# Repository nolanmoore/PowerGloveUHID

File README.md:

## Intro

In a world... where wires are a thing of the past, pound signs are now hashtags and there is always a “new black,” one man will revive a gaming icon in order to preserve the past… and control the future.

The ultimate goal of the Power Glove UHID (Universal Human Interface Device) project is to revamp the 1989 Nintendo Power Glove with modern sensors, giving you the ability to use gesture controls with almost anything you can think of, in style.

Check out the [Hackaday.io project page](https://hackaday.io/project/8455-power-glove-uhid) for more info!

## Revisions

### Main Board
* Rev 0.1 (current): Complete! Features custom keypad, Teensy 3/LC header, ESP-12E/01 headers and Pololu 3.3V step up/down regulator.<br />
Top side:<br />
<br />
Bottom side:<br />

### Sensor Board
* Rev 0.1 (current): Unfinished WIP. Along with the existing flex sensors, the current prototype sensor board will feature a Pololu AltIMU-10 as the main sensor.

## License

This is an open hardware design licensed under the terms of the CERN Open Hardware Licence (OHL) v1.2.

You may redistribute and modify this documentation under the terms of the CERN OHL v.1.2 (http://ohwr.org/cernohl). This documentation is distributed WITHOUT ANY EXPRESS OR IMPLIED WARRANTY, INCLUDING OF MERCHANTABILITY, SATISFACTORY QUALITY AND FITNESS FOR A PARTICULAR PURPOSE. Please see the CERN OHL v.1.2 for applicable conditions.

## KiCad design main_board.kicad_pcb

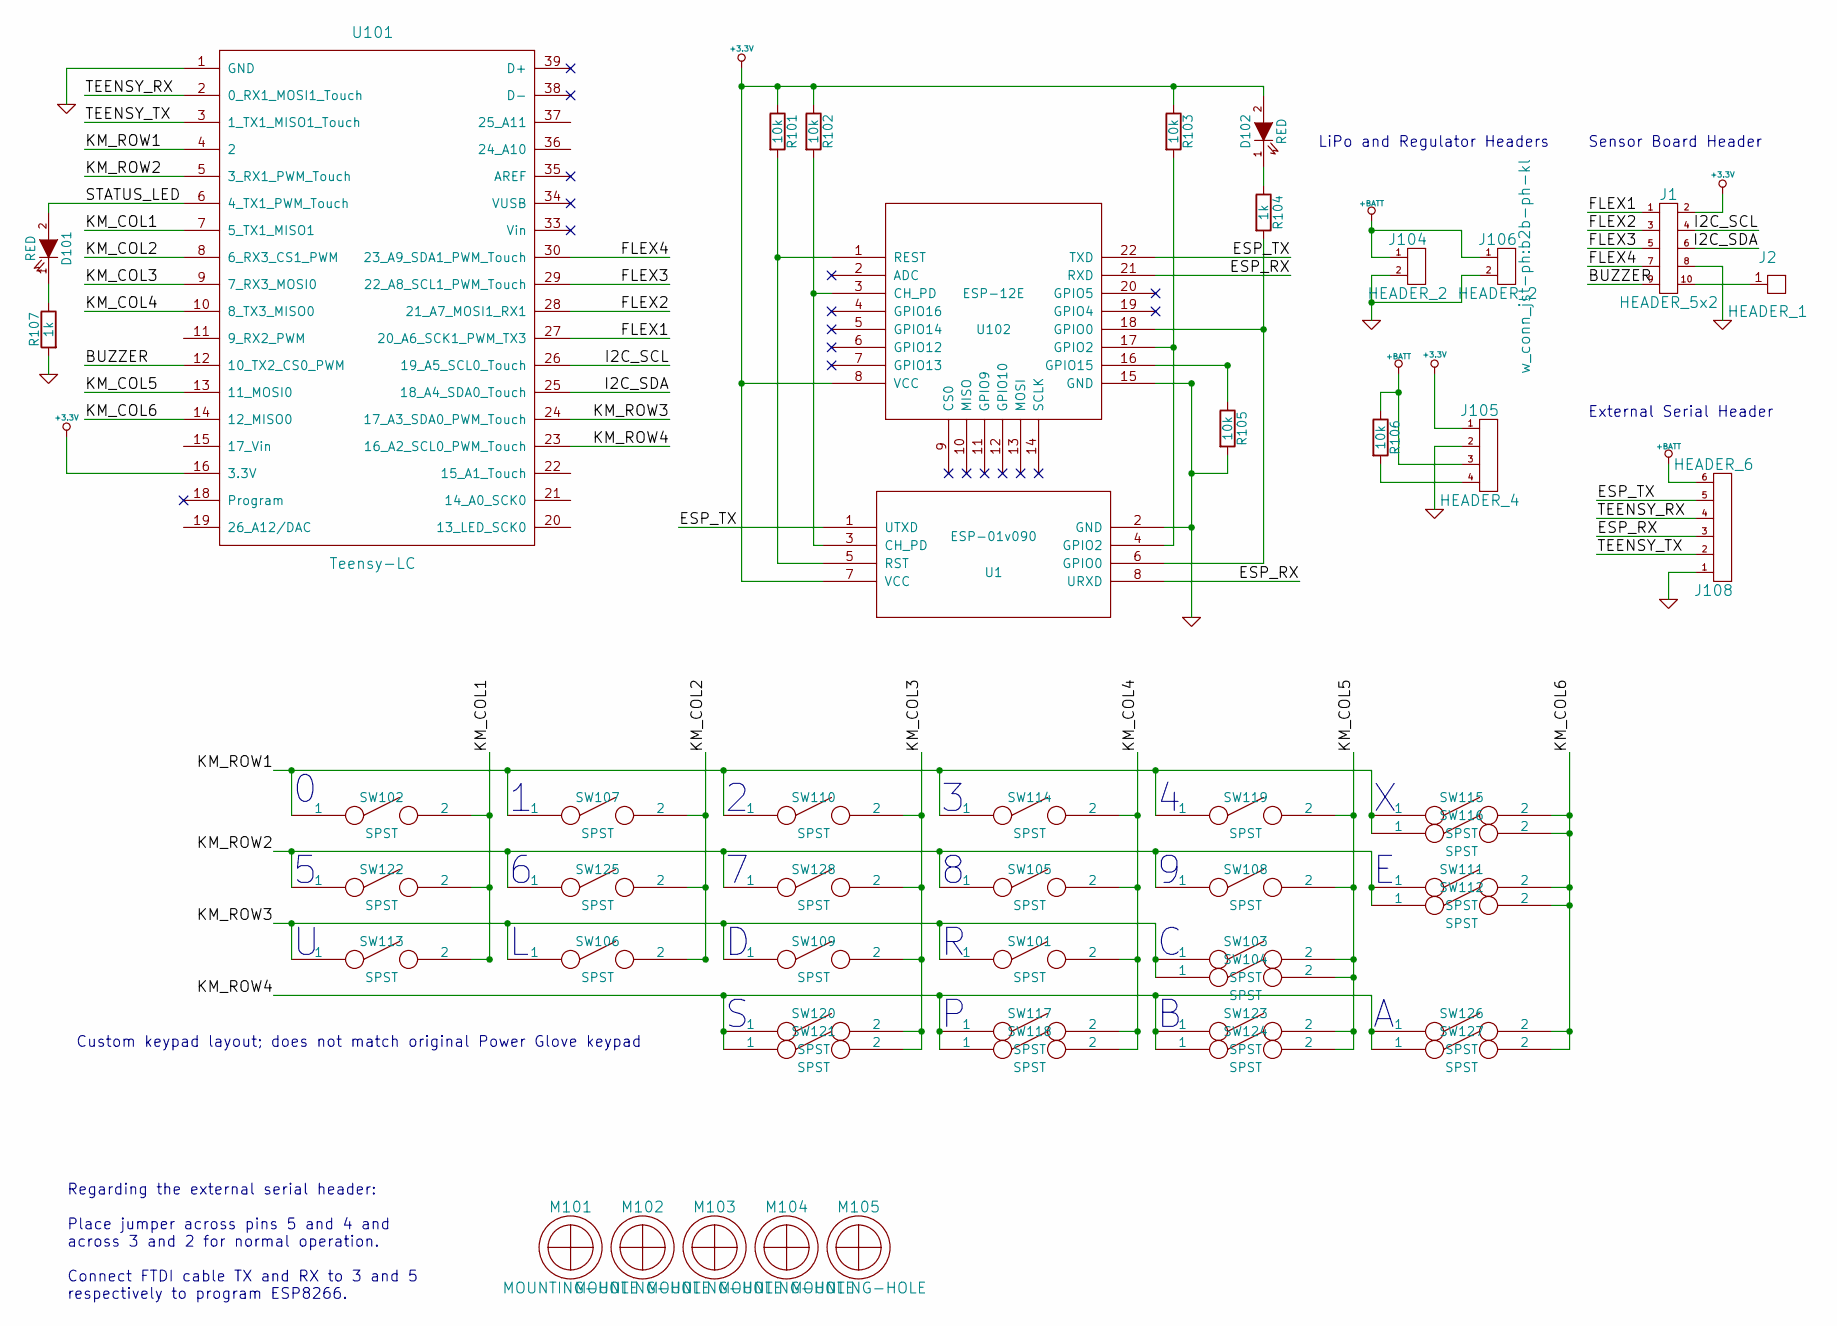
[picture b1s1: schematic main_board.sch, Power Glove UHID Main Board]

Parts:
D101: RED; LED-3MM
D102: RED; LED_0805
J1: HEADER_5x2; Socket_Strip_Straight_2x05
J2: HEADER_1; Socket_Strip_Straight_1x01
J104: HEADER_2; Socket_Strip_Straight_1x02
J105: HEADER_4; Socket_Strip_Straight_1x04
J106: HEADER_2; b2b-ph-kl
J108: HEADER_6; Pin_Header_Angled_1x06
M101, M102, M103, M104, M105: MOUNTING-HOLE; MountingHole_2-2mm
R101, R102, R103, R105, R106: 10k; R_0805
R104, R107: 1k; R_0805
SW101, SW106, SW109, SW113: SPST; CONDUCTIVE-PAD-HALFSHELL-150MIL
SW102, SW103, SW104, SW105, SW107, SW108, SW110, SW111, SW112, SW114, SW115, SW116, SW117, SW118, SW119, SW120, SW121, SW122, SW123, SW124, SW125, SW126, SW127, SW128: SPST; CONDUCTIVE-PAD-STANDARD-150MIL
U1: ESP-01v090; ESP-01
U101: Teensy-LC; Teensy3.x_LC
U102: ESP-12E

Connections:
+3.3V: D102.2 (A), J1.2, J105.1, R101.1, R102.1, R103.1, U1.7 (VCC), U101.16 (3.3V), U101.31 (3.3V), U102.8 (VCC)
+BATT: J104.1, J105.3, J106.1, J108.6, R106.1
/BUZZER: J1.9, U101.12 (10_TX2_CS0_PWM)
/ESP_RX: J108.3, U1.8 (URXD), U102.21 (RXD)
/ESP_TX: J108.5, U1.1 (UTXD), U102.22 (TXD)
/FLEX1: J1.1, U101.27 (20_A6_SCK1_PWM_TX3)
/FLEX2: J1.3, U101.28 (21_A7_MOSI1_RX1)
/FLEX3: J1.5, U101.29 (22_A8_SCL1_PWM_Touch)
/FLEX4: J1.7, U101.30 (23_A9_SDA1_PWM_Touch)
/I2C_SCL: J1.4, U101.26 (19_A5_SCL0_Touch)
/I2C_SDA: J1.6, U101.25 (18_A4_SDA0_Touch)
/KM_COL1: SW102.2, SW113.2, SW122.2, U101.7 (5_TX1_MISO1)
/KM_COL2: SW106.2, SW107.2, SW125.2, U101.8 (6_RX3_CS1_PWM)
/KM_COL3: SW109.2, SW110.2, SW120.2, SW121.2, SW128.2, U101.9 (7_RX3_MOSI0)
/KM_COL4: SW101.2, SW105.2, SW114.2, SW117.2, SW118.2, U101.10 (8_TX3_MISO0)
/KM_COL5: SW103.2, SW104.2, SW108.2, SW119.2, SW123.2, SW124.2, U101.13 (11_MOSI0)
/KM_COL6: SW111.2, SW112.2, SW115.2, SW116.2, SW126.2, SW127.2, U101.14 (12_MISO0)
/KM_ROW1: SW102.1, SW107.1, SW110.1, SW114.1, SW115.1, SW116.1, SW119.1, U101.4 (2)
/KM_ROW2: SW105.1, SW108.1, SW111.1, SW112.1, SW122.1, SW125.1, SW128.1, U101.5 (3_RX1_PWM_Touch)
/KM_ROW3: SW101.1, SW103.1, SW104.1, SW106.1, SW109.1, SW113.1, U101.24 (17_A3_SDA0_PWM_Touch)
/KM_ROW4: SW117.1, SW118.1, SW120.1, SW121.1, SW123.1, SW124.1, SW126.1, SW127.1, U101.23 (16_A2_SCL0_PWM_Touch)
/STATUS_LED: D101.2 (A), U101.6 (4_TX1_PWM_Touch)
/TEENSY_RX: J108.4, U101.2 (0_RX1_MOSI1_Touch)
/TEENSY_TX: J108.2, U101.3 (1_TX1_MISO1_Touch)
GND: J1.8, J104.2, J105.2, J106.2, J108.1, R105.2, R107.2, U1.2 (GND), U101.1 (GND), U101.17 (GND), U101.32 (GND), U102.15 (GND)
unnamed: D101.1 (K), R107.1
unnamed: D102.1 (K), R104.1
unnamed: J1.10, J2.1
unnamed: J105.4, R106.2
unnamed: R101.2, U1.5 (RST), U102.1 (REST)
unnamed: R102.2, U1.3 (CH_PD), U102.3 (CH_PD)
unnamed: R103.2, U1.4 (GPIO2), U102.17 (GPIO2)
unnamed: R104.2, U1.6 (GPIO0), U102.18 (GPIO0)
unnamed: R105.1, U102.16 (GPIO15)

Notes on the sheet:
Sensor Board Header
LiPo and Regulator Headers
Custom keypad layout; does not match original Power Glove keypad
External Serial Header
Regarding the external serial header: Place jumper across pins 5 and 4 and across 3 and 2 for normal operation. Connect FTDI cable TX and RX to 3 and 5 respectively to program ESP8266.

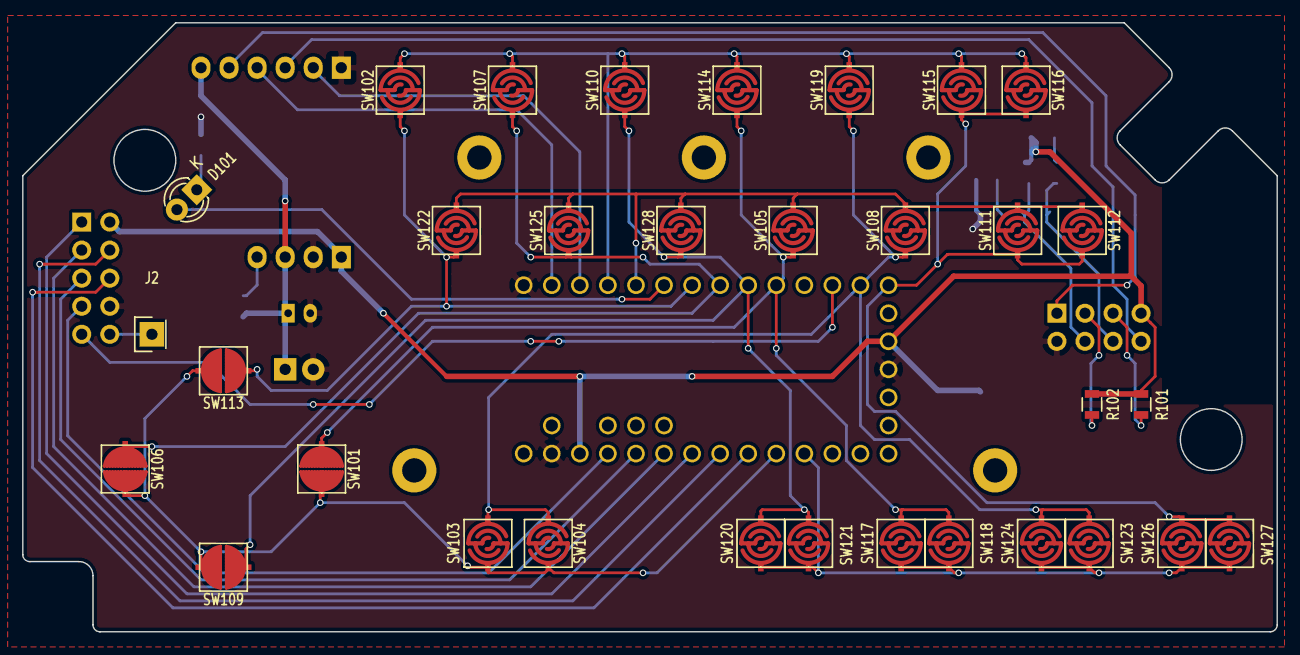
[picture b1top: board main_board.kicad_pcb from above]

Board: 2 copper layers, 113.5 x 55.1 mm, 51 parts (0 on the bottom side), 34 nets.

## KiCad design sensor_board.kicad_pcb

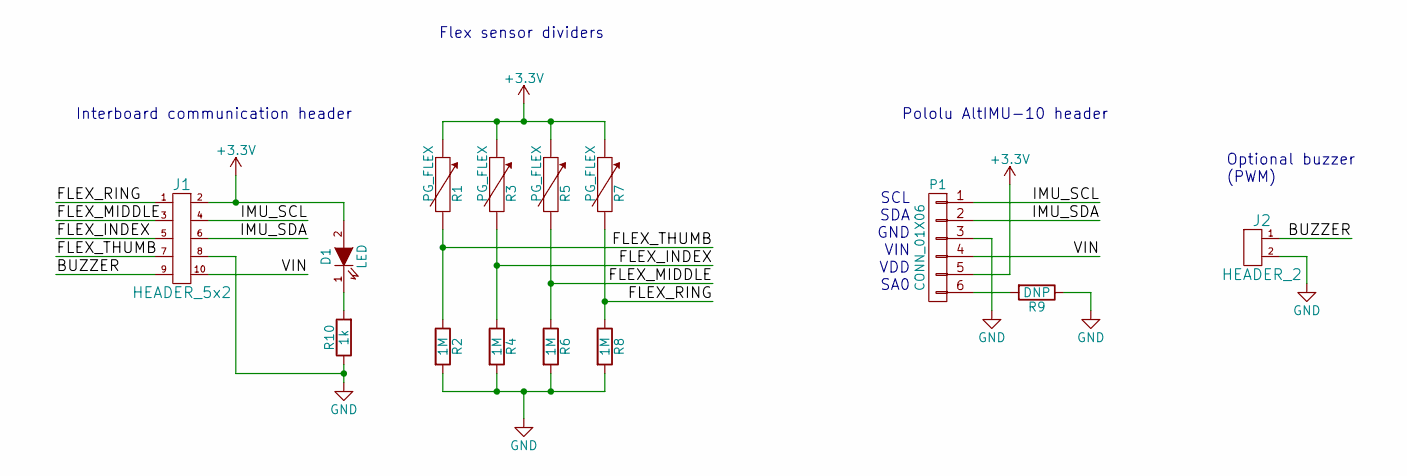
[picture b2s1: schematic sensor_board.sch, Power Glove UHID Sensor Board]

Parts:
D1: LED; Led_0805
J1: HEADER_5x2; Socket_Strip_Straight_2x05
J2: HEADER_2; Socket_Strip_Straight_1x02
P1: CONN_01X06; ALTIMU10
R1, R3, R5, R7: PG_FLEX; Socket_Strip_Straight_1x02
R2, R4, R6, R8: 1M; Resistor_Horizontal_RM10mm
R9: DNP; R_0805_HandSoldering
R10: 1k; R_0805_HandSoldering

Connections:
+3V3: D1.2 (A), J1.2, P1.5, R1.1, R3.1, R5.1, R7.1
/BUZZER: J1.9, J2.1
/FLEX_INDEX: J1.5, R3.2, R4.1
/FLEX_MIDDLE: J1.3, R5.2, R6.1
/FLEX_RING: J1.1, R7.2, R8.1
/FLEX_THUMB: J1.7, R1.2, R2.1
/IMU_SCL: J1.4, P1.1
/IMU_SDA: J1.6, P1.2
/VIN: J1.10, P1.4
GND: J1.8, J2.2, P1.3, R2.2, R4.2, R6.2, R8.2, R9.1, R10.1
unnamed: D1.1 (K), R10.2
unnamed: P1.6, R9.2

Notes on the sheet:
SCL SDA GND VIN VDD SA0
Flex sensor dividers
Interboard communication header
Pololu AltIMU-10 header
Optional buzzer (PWM)

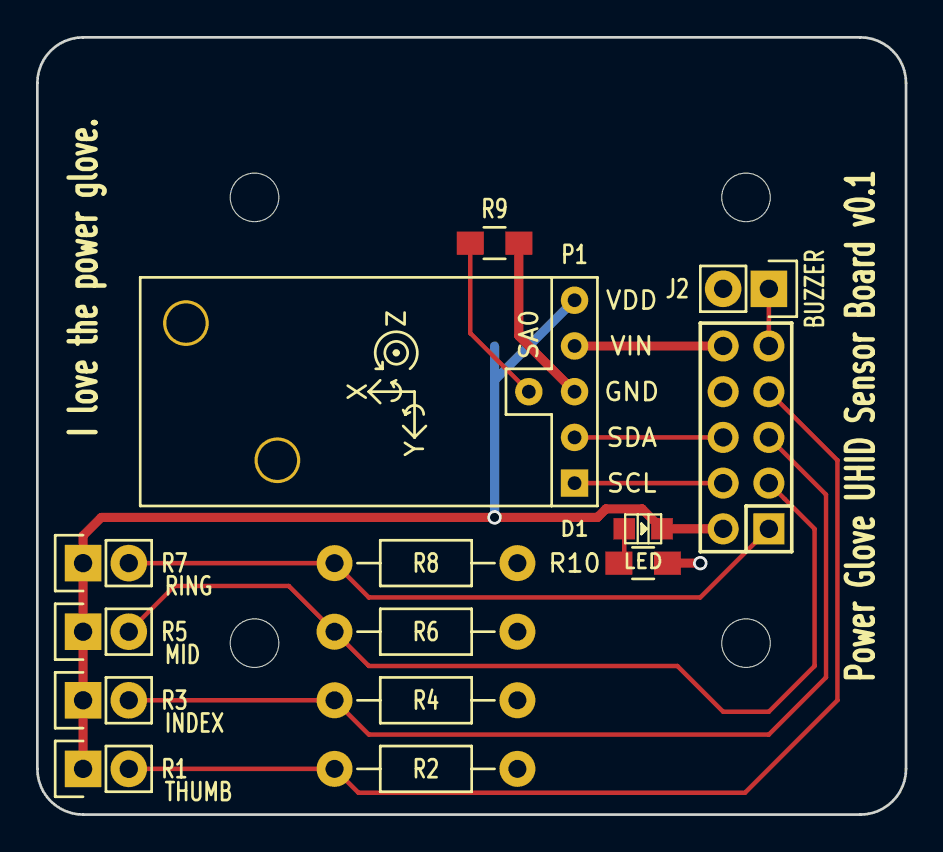
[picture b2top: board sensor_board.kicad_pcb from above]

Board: 2 copper layers, 48.3 x 43.2 mm, 14 parts (1 on the bottom side), 12 nets.

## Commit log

2016-03-13 Initial upload, everything still WIP
    I do NOT advise you to send these to OSH just yet
2016-03-13 Delete LICENSE
    Moving to a different license (to be mentioned in the readme)
2016-03-21 Final main board v0.1
    Last big upload commit before I start doing proper commits ;)
2016-03-21 Updated project module library
2016-03-21 Cleaned up schematics and sensor board PCB
2016-03-21 Readme update, added renders of current prototypes
2016-03-21 Update README.md
    adjusted image sizes
2016-03-21 Update README.md
    even more readme fixes
2016-03-23 Sensor board revised fit within a 5cmX5cm square
2016-03-24 Rearranged sensor board components for cleanliness
2016-03-24 Sensor board images added, gerbers plotted
2016-04-02 Bumped version to 0.2, cleaned schematic, added voltage divider resistors, boot and reset buttons
